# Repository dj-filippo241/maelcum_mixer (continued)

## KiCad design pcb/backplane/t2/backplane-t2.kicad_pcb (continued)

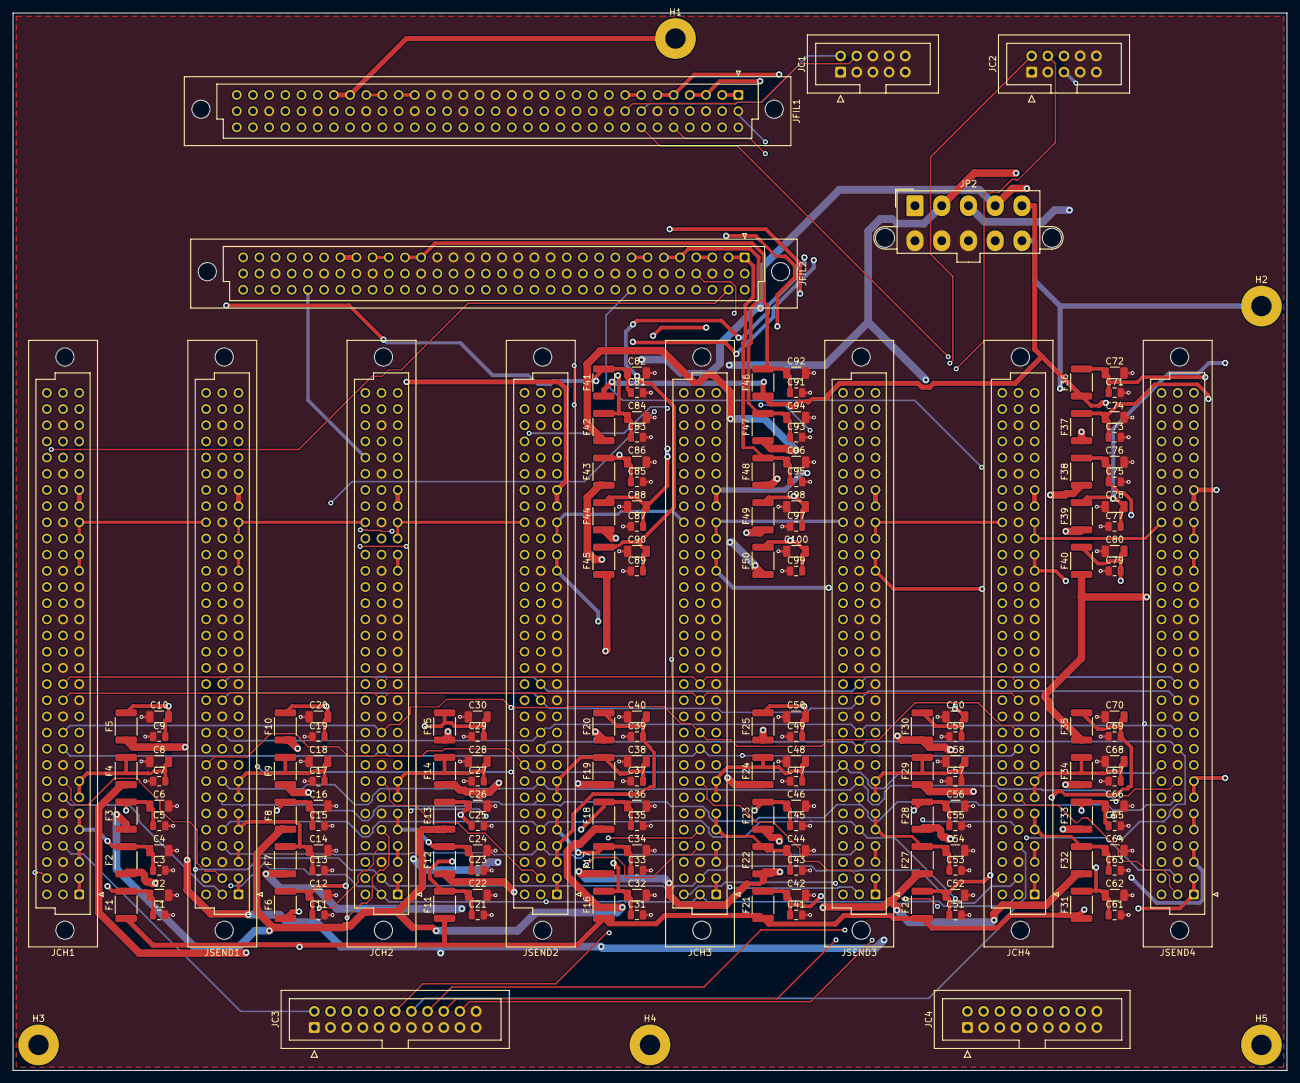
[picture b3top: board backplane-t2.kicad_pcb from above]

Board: 4 copper layers, 200.0 x 166.0 mm, 170 parts (0 on the bottom side), 99 nets.

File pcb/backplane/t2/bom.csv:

quantita;valore;impronta;riferimenti;nota
50;100n 50V;C_0805_2012Metric;C1 C3 C5 C7 C9 C11 C13 C15 C17 C19 C21 C23 C25 C27 C29 C31 C33 C35 C37 C39 C41 C43 C45 C47 C49 C51 C53 C55 C57 C59 C61 C63 C65 C67 C69 C71 C73 C75 C77 C79 C81 C83 C85 C87 C89 C91 C93 C95 C97 C99;bypass di slot (backplane §8)
50;10u 50V X7R;C_1206_3216Metric;C2 C4 C6 C8 C10 C12 C14 C16 C18 C20 C22 C24 C26 C28 C30 C32 C34 C36 C38 C40 C42 C44 C46 C48 C50 C52 C54 C56 C58 C60 C62 C64 C66 C68 C70 C72 C74 C76 C78 C80 C82 C84 C86 C88 C90 C92 C94 C96 C98 C100;bulk di slot (backplane §8); NOTA: MLCC 50 V
4;PTC 0.2 A;Fuse_1812_4532Metric;F1 F11 F21 F31;PTC di slot (psu-esterno §4.3); NOTA: tenuta 0.2 A, >= 33 V, 1812
18;PTC 0.1 A;Fuse_1812_4532Metric;F2 F4 F8 F10 F12 F14 F18 F20 F22 F24 F28 F30 F32 F34 F38 F40 F41 F46;PTC di slot (psu-esterno §4.3); NOTA: tenuta 0.1 A, >= 33 V, 1812
16;PTC 0.3 A;Fuse_1812_4532Metric;F3 F5 F13 F15 F23 F25 F33 F35 F42 F43 F44 F45 F47 F48 F49 F50;PTC di slot (psu-esterno §4.3); NOTA: tenuta 0.3 A, >= 33 V, 1812
12;PTC 0.05 A;Fuse_1812_4532Metric;F6 F7 F9 F16 F17 F19 F26 F27 F29 F36 F37 F39;PTC di slot (psu-esterno §4.3); NOTA: tenuta 0.05 A, >= 33 V, 1812
1;cavo C1 T1-T2 (VE);IDC-Header_2x05_P2.54mm_Vertical;JC1;NOTA: cavo piatto, ogni segnale fra due fili di massa; solo net a massa virtuale
1;cavo C2 T1-T2 (pilotato);IDC-Header_2x05_P2.54mm_Vertical;JC2;NOTA: cavo piatto, ogni segnale fra due fili di massa; solo linee pilotate
1;cavo C3 T2-T3 (pilotato);IDC-Header_2x11_P2.54mm_Vertical;JC3;NOTA: cavo piatto, ogni segnale fra due fili di massa; solo linee pilotate
1;cavo C4 T2-T4 (VE);IDC-Header_2x09_P2.54mm_Vertical;JC4;NOTA: cavo piatto, ogni segnale fra due fili di massa; solo net a massa virtuale
1;C96 femmina CH1;DIN41612_C_3x32_Female_Vertical_THT;JCH1;slot CH1, classe canale; pin da pcb/canale (netlist). Fila a a 2.11 mm dal piano medio della scheda di modulo, lato F del modulo verso la fila c (Harting 09 03 196 6921)
1;C96 femmina CH2;DIN41612_C_3x32_Female_Vertical_THT;JCH2;slot CH2, classe canale; pin da pcb/canale (netlist). Fila a a 2.11 mm dal piano medio della scheda di modulo, lato F del modulo verso la fila c (Harting 09 03 196 6921)
1;C96 femmina CH3;DIN41612_C_3x32_Female_Vertical_THT;JCH3;slot CH3, classe canale; pin da pcb/canale (netlist). Fila a a 2.11 mm dal piano medio della scheda di modulo, lato F del modulo verso la fila c (Harting 09 03 196 6921)
1;C96 femmina CH4;DIN41612_C_3x32_Female_Vertical_THT;JCH4;slot CH4, classe canale; pin da pcb/canale (netlist). Fila a a 2.11 mm dal piano medio della scheda di modulo, lato F del modulo verso la fila c (Harting 09 03 196 6921)
1;C96 femmina FIL1;DIN41612_C_3x32_Female_Vertical_THT;JFIL1;slot FIL1, classe filtro; pin da pcb/filtro/HPF (netlist). Fila a a 2.11 mm dal piano medio della scheda di modulo, lato F del modulo verso la fila c (Harting 09 03 196 6921)
1;C96 femmina FIL2;DIN41612_C_3x32_Female_Vertical_THT;JFIL2;slot FIL2, classe filtro; pin da pcb/filtro/LPF (netlist). Fila a a 2.11 mm dal piano medio della scheda di modulo, lato F del modulo verso la fila c (Harting 09 03 196 6921)
1;potenza P2 T1-T2;Molex_Mini-Fit_Jr_5566-10A2_2x05_P4.20mm_Vertical;JP2;NOTA: Mini-Fit Jr 2x5; radiale AGND del tratto fino alla stella del PSU-IN (grounding §2)
1;C96 femmina SEND1;DIN41612_C_3x32_Female_Vertical_THT;JSEND1;slot SEND1, classe fx-send; pin da pcb/fx-send (netlist). Fila a a 2.11 mm dal piano medio della scheda di modulo, lato F del modulo verso la fila c (Harting 09 03 196 6921)
1;C96 femmina SEND2;DIN41612_C_3x32_Female_Vertical_THT;JSEND2;slot SEND2, classe fx-send; pin da pcb/fx-send (netlist). Fila a a 2.11 mm dal piano medio della scheda di modulo, lato F del modulo verso la fila c (Harting 09 03 196 6921)
1;C96 femmina SEND3;DIN41612_C_3x32_Female_Vertical_THT;JSEND3;slot SEND3, classe fx-send; pin da pcb/fx-send (netlist). Fila a a 2.11 mm dal piano medio della scheda di modulo, lato F del modulo verso la fila c (Harting 09 03 196 6921)
1;C96 femmina SEND4;DIN41612_C_3x32_Female_Vertical_THT;JSEND4;slot SEND4, classe fx-send; pin da pcb/fx-send (netlist). Fila a a 2.11 mm dal piano medio della scheda di modulo, lato F del modulo verso la fila c (Harting 09 03 196 6921)

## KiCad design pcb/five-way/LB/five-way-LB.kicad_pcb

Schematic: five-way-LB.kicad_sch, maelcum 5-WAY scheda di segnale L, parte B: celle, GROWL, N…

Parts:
C1, C2: 220u 35V; CP_Radial_D8.0mm_P3.50mm
C3: 47u 10V; CP_Radial_D5.0mm_P2.00mm
C4, C8: 10u 35V; CP_Radial_D5.0mm_P2.00mm
C5, C9: 47u 35V; CP_Radial_D6.3mm_P2.50mm
C6, C10: 470u 25V; CP_Radial_D8.0mm_P3.50mm
C7, C11: 100u 25V; CP_Radial_D6.3mm_P2.50mm
C12, C13: 1u 50V; C_1206_3216Metric
C14, C15: 1u 25V; C_1206_3216Metric
C16, C17, C19, C20: 4u7 25V; C_1206_3216Metric
C18, C21: 10u 25V; C_1206_3216Metric
C22: 1u; C_1206_3216Metric
C23, C24, C25, C26, C27, C28, C29, C30, C35, C36, C37, C38, C39, C40, C45, C46, C47, C48, C49, C50, C55, C56, C57, C58, C59, C60, C65, C66, C67, C68, C69, C70, C75, C76, C77, C78, C79, C80, C88, C89, C90, C91, C104, C105, C106, C107, C108, C109, C110, C111, C113, C114: 100n; C_0805_2012Metric
C31, C33: 680n film; C_1812_4532Metric
C32, C34, C42, C44, C52, C54, C62, C64, C72, C74, C81, C83, C112: 100n film; C_1812_4532Metric
C41, C43, C101, C102, C103: 180n film; C_1812_4532Metric
C51, C53: 56n film; C_1812_4532Metric
C61, C63: 18n C0G; C_1206_3216Metric
C71, C73: 4n7 C0G; C_1206_3216Metric
C82, C84: 47n film; C_1812_4532Metric
C85: 6n8 C0G; C_1206_3216Metric
C86: 22u NP; CP_Radial_D6.3mm_P2.50mm
C87: 10u NP; CP_Radial_D6.3mm_P2.50mm
C92, C93, C94: 150n film; C_1812_4532Metric
C95: 1n5 C0G; C_1206_3216Metric
C96, C100: 5n1 C0G; C_1206_3216Metric
C97: 2200u 10V; CP_Radial_D10.0mm_P5.00mm
C98: 10u 25V; CP_Radial_D5.0mm_P2.00mm
C99: 1n8 C0G; C_1206_3216Metric
D1, D3, D6, D7, D8, D9, D10, D11, D12, D13, D14, D15, D16, D17, D18, D19, D20, D21, D22, D23, D24, D25, D26, D27, D28, D29, D30: 1N4148W; D_SOD-123
D2, D4: S1G; D_SMA
D5: LM4040-5.0; SOT-23
FB1, FB2, FB3, FB4, FB5: ferrite 600R; L_1206_3216Metric
H1, H2, H3: CHASSIS; MountingHole_3.2mm_M3_Pad
J1: C96 maschio; DIN41612_C_3x32_Male_Horizontal_THT
J2: 2x31 cavo piatto; PinHeader_2x31_P2.54mm_Vertical
Q1, Q2, Q3, Q4, Q5, Q6, Q7, Q8, Q9, Q10: LSK389 (dual); SOIC-8_3.9x4.9mm_P1.27mm
Q11: MMBFJ310; SOT-23
Q140: BD139; TO-126-3_Vertical
Q141: BD140; TO-126-3_Vertical
R1, R4: 120 1%; R_0805_2012Metric
R2, R5: 1k74 1%; R_0805_2012Metric
R3, R6, R242: 1k; R_0805_2012Metric
R7, R8: 150k 0.1%; R_0805_2012Metric
R9, R213: 1k5; R_0805_2012Metric
R10, R11, R23, R33, R43, R53, R63, R65, R67, R84, R85, R87, R89, R106, R107, R109, R111, R128, R129, R131, R133, R150, R151, R153, R155, R172, R173, R178, R179, R180, R181, R193, R194, R195, R201, R203, R205, R207, R209, R219, R221, R222, R224, R226, R228, R230, R231, R238: 10k 0.1%; R_0805_2012Metric
R12, R22, R32, R42, R52, R62: 49k9 0.1%; R_0805_2012Metric
R13: 1k02 0.1%; R_0805_2012Metric
R14, R24, R34, R44, R54, R241: 100k; R_0805_2012Metric
R15, R35: 24k3 0.1%; R_0805_2012Metric
R16, R36, R200, R202, R204: 36k5 0.1%; R_0805_2012Metric
R17, R37: 267k 0.1%; R_0805_2012Metric
R18, R38: 22k1 0.1%; R_0805_2012Metric
R19, R39: 57k6 0.1%; R_0805_2012Metric
R20, R40: 13k0 0.1%; R_0805_2012Metric
R21, R41, R48: 20k5 0.1%; R_0805_2012Metric
R25: 27k4 0.1%; R_0805_2012Metric
R26: 47k5 0.1%; R_0805_2012Metric
R27: 340k 0.1%; R_0805_2012Metric
R28, R66, R88, R110, R132, R154: 30k1 0.1%; R_0805_2012Metric
R29: 76k8 0.1%; R_0805_2012Metric
R30, R51, R58: 18k7 0.1%; R_0805_2012Metric
R31: 28k7 0.1%; R_0805_2012Metric
R45: 23k7 0.1%; R_0805_2012Metric
R46: 34k8 0.1%; R_0805_2012Metric
R47: 255k 0.1%; R_0805_2012Metric
R49: 53k6 0.1%; R_0805_2012Metric
R50: 12k1 0.1%; R_0805_2012Metric
R55: 23k2 0.1%; R_0805_2012Metric
R56: 32k4 0.1%; R_0805_2012Metric
R57: 232k 0.1%; R_0805_2012Metric
R59: 48k7 0.1%; R_0805_2012Metric
R60: 10k7 0.1%; R_0805_2012Metric
R61: 16k9 0.1%; R_0805_2012Metric
R64, R86, R108, R130, R152: 40k2 0.1%; R_0805_2012Metric
R68, R69, R70, R71, R73, R74, R75, R76, R90, R91, R92, R93, R95, R96, R97, R98, R112, R113, R114, R115, R117, R118, R119, R120, R134, R135, R136, R137, R139, R140, R141, R142, R156, R157, R158, R159, R161, R162, R163, R164: 100k 0.1%; R_0805_2012Metric
R72, R77: 117k 0.1%; R_0805_2012Metric
R78, R100, R122, R144, R166: 110 0.1%; R_0805_2012Metric
R79, R101, R123, R145, R167: 1k8 0.1%; R_0805_2012Metric
R80, R102, R124, R146, R168: 200 0.1%; R_0805_2012Metric
R81, R82, R103, R104, R125, R126, R147, R148, R169, R170, R206: 2k 0.1%; R_0805_2012Metric
R83, R105, R127, R149, R171: 1k62 0.1%; R_0805_2012Metric
R94, R99, R138, R143: 110k 0.1%; R_0805_2012Metric
R116, R121, R160, R165: 113k 0.1%; R_0805_2012Metric
R174, R175, R176, R177, R182: 9k31 0.1%; R_0805_2012Metric
R183, R210: 1k 0.1%; R_0805_2012Metric
R184: 47k; R_0805_2012Metric
R185, R186: 470; R_0805_2012Metric
R187, R229: 4k99 0.1%; R_0805_2012Metric
R188, R212: 10k; R_0805_2012Metric
R189, R190: 4k7; R_0805_2012Metric
R191: 11k1 0.1%; R_0805_2012Metric
R192, R208, R220, R239: 20k 0.1%; R_0805_2012Metric
R196, R233, R240: 1M; R_0805_2012Metric
R197, R198, R199, R234, R235, R236: 2k2 0.1%; R_0805_2012Metric
R211: 7k5; R_0805_2012Metric
R214: 150; R_0805_2012Metric
R215: 910; R_0805_2012Metric
R216: 48k7; R_0805_2012Metric
R217: 9k53; R_0805_2012Metric
R218: 4k87 0.1%; R_0805_2012Metric
R223, R225, R227: 19k6 0.1%; R_0805_2012Metric
R232: 1k8; R_0805_2012Metric
R237: 33; R_0805_2012Metric
R243: 47; R_0805_2012Metric
R244: 100; R_0805_2012Metric
U1, U2, U3, U5, U6, U8, U9, U11, U12, U14, U15, U17, U18, U19, U20, U21, U22, U23: OPA1654AIDR; SOIC-14_3.9x8.7mm_P1.27mm
U4, U7, U10, U13, U16, U24, U146: OPA1612AIDR; SOIC-8_3.9x4.9mm_P1.27mm
U25: OPA1642AIDR; SOIC-8_3.9x4.9mm_P1.27mm
U140: LM317; TO-220-3_Vertical
U141: LM337; TO-220-3_Vertical
U142: 78L15; SOT-89-3
U143: 79L15; SOT-89-3
U144: LT3045EMSE; MSOP-12-1EP_3x4.039mm_P0.65mm_EP1.651x2.845mm
U145: LT3094EMSE; MSOP-12-1EP_3x4.039mm_P0.65mm_EP1.651x2.845mm

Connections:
5W_MET_L: J2.55, R244.2
5W_OUT_L: J1.b4, R243.2
5W_SUM_L: J1.b7, R64.1, R84.1
+5V: FB5.1, J1.a21, J1.a22
+5VF: C3.1, FB5.2, J2.60
+15LN: C18.1, C23.1, C25.1, C27.1, C29.1, J2.57, R9.1, U1.4 (V+), U2.4 (V+), U3.4 (V+), U144.10 (OUTS), U144.11 (OUT), U144.12 (OUT), U146.8 (V+)
+15SW: C14.1, U142.1 (OUT)
+18V: C7.1, C17.1, C35.1, C37.1, C39.1, C45.1, C47.1, C49.1, C55.1, C57.1, C59.1, C65.1, C67.1, C69.1, C75.1, C77.1, C79.1, C88.1, C90.1, C104.1, C106.1, C108.1, C110.1, C113.1, Q140.1 (E), R213.1, U4.8 (V+), U5.4 (V+), U6.4 (V+), U7.8 (V+), U8.4 (V+), U9.4 (V+), U10.8 (V+), U11.4 (V+), U12.4 (V+), U13.8 (V+), U14.4 (V+), U15.4 (V+), U16.8 (V+), U17.4 (V+), U18.4 (V+), U19.4 (V+), U20.4 (V+), U21.4 (V+), U22.4 (V+), U23.4 (V+), U24.8 (V+), U25.8 (V+), U144.1 (IN), U144.2 (IN), U144.3 (IN), U144.4 (EN/UV), U144.7 (PGFB)
+REF5: J2.2, R10.1, R12.1, R22.1, R32.1, R42.1, R52.1, R62.1, U146.1, U146.2 (-)
-15LN: C21.2, C24.2, C26.2, C28.2, C30.2, J2.59, U1.11 (V-), U2.11 (V-), U3.11 (V-), U145.10 (OUTS), U145.11 (OUT), U145.12 (OUT), U146.4 (V-)
-15SW: C15.2, U143.3 (VO)
-18V: C11.2, C20.2, C36.2, C38.2, C40.2, C46.2, C48.2, C50.2, C56.2, C58.2, C60.2, C66.2, C68.2, C70.2, C76.2, C78.2, C80.2, C89.2, C91.2, C105.2, C107.2, C109.2, C111.2, C114.2, Q141.1 (E), U4.4 (V-), U5.11 (V-), U6.11 (V-), U7.4 (V-), U8.11 (V-), U9.11 (V-), U10.4 (V-), U11.11 (V-), U12.11 (V-), U13.4 (V-), U14.11 (V-), U15.11 (V-), U16.4 (V-), U17.11 (V-), U18.11 (V-), U19.11 (V-), U20.11 (V-), U21.11 (V-), U22.11 (V-), U23.11 (V-), U24.4 (V-), U25.4 (V-), U145.1 (IN), U145.2 (IN), U145.3 (EN/UV), U145.5 (PGFB), U145.13 (IN)
-REF5: R11.2, R17.2, R19.2, R21.2, R27.2, R29.2, R31.2, R37.2, R39.2, R41.2, R47.2, R49.2, R51.2, R57.2, R59.2, R61.2, U146.7
ADJ+: C4.1, D1.2 (A), R1.2, R2.1, U140.1 (ADJ)
ADJ-: C8.2, D3.1 (K), R4.2, R5.1, U141.1 (ADJ)
AGND: C1.2, C2.1, C4.2, C5.2, C6.2, C7.2, C8.1, C9.1, C10.1, C11.1, C12.2, C13.1, C14.2, C15.1, C16.2, C17.2, C18.2, C19.1, C20.1, C21.1, C22.2, C23.2, C24.1, C25.2, C26.1, C27.2, C28.1, C29.2, C30.1, C35.2, C36.1, C37.2, C38.1, C39.2, C40.1, C45.2, C46.1, C47.2, C48.1, C49.2, C50.1, C55.2, C56.1, C57.2, C58.1, C59.2, C60.1, C65.2, C66.1, C67.2, C68.1, C69.2, C70.1, C75.2, C76.1, C77.2, C78.1, C79.2, C80.1, C82.2, C84.2, C85.2, C88.2, C89.1, C90.2, C91.1, C95.2, C96.2, C97.2, C99.2, C100.2, C104.2, C105.1, C106.2, C107.1, C108.2, C109.1, C110.2, C111.1, C113.2, C114.1, D5.2 (A), J1.a13, J1.a14, J1.a15, J1.a16, J1.a17, J1.a18, J1.a19, J1.a20, J1.b3, J1.b6, J1.b9, J1.b12, J1.b15, J1.b18, J1.b21, J1.b24, J1.b27, J1.b30, J2.1, J2.10, J2.18, J2.26, J2.34, J2.42, J2.49, J2.54, J2.56, J2.58, J2.62, R2.2, R5.2, R7.2, R8.2, R13.2, R14.2, R24.2, R34.2, R44.2, R54.2, R78.2, R80.2, R100.2, R102.2, R122.2, R124.2, R144.2, R146.2, R166.2, R168.2, R179.2, R196.2, R201.2, R203.2, R205.2, R210.2, R215.2, R222.2, R224.2, R226.2, R229.2, R233.2, R242.2, U1.10 (+), U2.3 (+), U2.10 (+), U3.3 (+), U3.10 (+), U3.12 (+), U4.5 (+), U5.3 (+), U5.5 (+), U5.12 (+), U6.3 (+), U6.10 (+), U6.12 (+), U7.5 (+), U8.3 (+), U8.5 (+), U8.12 (+), U9.3 (+), U9.10 (+), U9.12 (+), U10.5 (+), U11.3 (+), U11.5 (+), U11.12 (+), U12.3 (+), U12.10 (+), U12.12 (+), U13.5 (+), U14.3 (+), U14.5 (+), U14.12 (+), U15.3 (+), U15.10 (+), U15.12 (+), U16.5 (+), U17.3 (+), U17.5 (+), U17.12 (+), U18.3 (+), U18.10 (+), U18.12 (+), U20.3 (+), U20.5 (+), U20.10 (+), U22.5 (+), U24.3 (+), U24.5 (+), U25.5 (+), U142.2 (GND), U143.1 (GND), U144.6 (ILIM), U144.9 (GND), U144.13 (GND), U145.6 (ILIM), U145.9 (GND), U146.5 (+)
BASE+: C6.1, Q140.3 (B), R3.2
BASE-: C10.2, Q141.3 (B), R6.2
BP1: C31.2, U5.7, U5.10 (+)
BP2: C41.2, U8.7, U8.10 (+)
BP3: C51.2, U11.7, U11.10 (+)
BP4: C61.2, U14.7, U14.10 (+)
BP5: C71.2, U17.7, U17.10 (+)
BPB1: J2.4, Q2.2 (D1), R73.1, U5.8, U5.9 (-)
BPB2: J2.12, Q4.2 (D1), R95.1, U8.8, U8.9 (-)
BPB3: J2.20, Q6.2 (D1), R117.1, U11.8, U11.9 (-)
BPB4: J2.28, Q8.2 (D1), R139.1, U14.8, U14.9 (-)
BPB5: J2.36, Q10.2 (D1), R161.1, U17.8, U17.9 (-)
CHASSIS: H1.1, H2.1, H3.1, J1.a25, J1.a26
CTRL_GND: C3.2, J1.a23, J1.a24, J1.c16, J1.c20, J1.c24, J1.c28, J2.61
DBG: R198.1, U20.13 (-), U20.14
DBT: R235.1, U23.13 (-), U23.14
DDG: J2.43, R195.2, U20.8
DQ1: J2.7, R79.1, R81.1, U4.1
DQ2: J2.15, R101.1, R103.1, U7.1
DQ3: J2.23, R123.1, R125.1, U10.1
DQ4: J2.31, R145.1, R147.1, U13.1
DQ5: J2.39, R167.1, R169.1, U16.1
DS1N: R197.2, R198.2, R199.1, U24.2 (-)
DS2N: R234.2, R235.2, R236.1, U24.6 (-)
DSEL: R231.2, R232.1, U23.8
DTP: J2.50, R232.2
DWG: J2.44, R196.1, U20.12 (+)
DWT: J2.51, R233.1, U23.12 (+)
DY1: C92.1, R199.2, R200.1, R230.1, R234.1, U24.1
DY2: R236.2, R237.1, U24.7
E1: R85.2, R86.1, R106.1, U6.14
E2: R107.2, R108.1, R128.1, U9.14
E3: R129.2, R130.1, R150.1, U12.14
E4: R151.2, R152.1, R172.1, U15.14
E5: R173.2, R174.1, R178.1, R197.1, U18.14
EDRV: R237.2, R238.1, R244.1
GA1: C81.1, R174.2, R175.1
GA2: C82.1, R175.2, U19.3 (+)
GB1: C83.1, R176.2, R177.1
GB2: C84.1, R177.2, U19.5 (+)
GDN: R191.2, R192.2, R193.2, R194.2, R195.1, U20.9 (-)
GLA1: D21.1 (K), R185.1
GLAC: C86.2, R191.1
GLB1: D22.1 (K), D23.2 (A)
GLB2: D23.1 (K), D24.2 (A)
GLB3: D24.1 (K), R186.1
GLGN: D21.2 (A), R183.2, R184.1, R186.2, U20.2 (-)
GLOUT: C86.1, D22.2 (A), R184.2, R185.2, U20.1
GLOW: C83.2, J2.45, R180.1, R193.1, U19.6 (-), U19.7
GLP1: C81.2, R176.1, U19.1, U19.2 (-)
GLR: J2.46, R183.1
GMA1: D25.1 (K), D26.2 (A)
GMA2: D26.1 (K), D27.2 (A)
GMA3: D27.1 (K), R189.1
GMAC: C87.2, R192.1
GMB1: D28.1 (K), D29.2 (A)
GMB2: D29.1 (K), D30.2 (A)
GMB3: D30.1 (K), R190.1
GMC: C85.1, R182.2, U19.12 (+)
GMGN: D25.2 (A), R187.2, R188.1, R190.2, U20.6 (-)
GMID: J2.47, R194.1, U19.13 (-), U19.14
GMOUT: C87.1, D28.2 (A), R188.2, R189.2, U20.7
GMR: J2.48, R187.1
GR1_1: Q1.8 (G2), R70.2, R71.2
GR1_2: Q2.8 (G2), R75.2, R76.2
GR2_1: Q3.8 (G2), R92.2, R93.2
GR2_2: Q4.8 (G2), R97.2, R98.2
GR3_1: Q5.8 (G2), R114.2, R115.2
GR3_2: Q6.8 (G2), R119.2, R120.2
GR4_1: Q7.8 (G2), R136.2, R137.2
GR4_2: Q8.8 (G2), R141.2, R142.2
GR5_1: Q9.8 (G2), R158.2, R159.2
GR5_2: Q10.8 (G2), R163.2, R164.2
GREST: R181.2, R182.1, U19.8
GRN: R180.2, R181.1, U19.9 (-)
GRP: R178.2, R179.1, U19.10 (+)
GS1_1: Q1.4 (G1), R68.2, R69.2
GS1_2: Q2.4 (G1), R73.2, R74.2
GS2_1: Q3.4 (G1), R90.2, R91.2
GS2_2: Q4.4 (G1), R95.2, R96.2
GS3_1: Q5.4 (G1), R112.2, R113.2
GS3_2: Q6.4 (G1), R117.2, R118.2
GS4_1: Q7.4 (G1), R134.2, R135.2
GS4_2: Q8.4 (G1), R139.2, R140.2
GS5_1: Q9.4 (G1), R156.2, R157.2
GS5_2: Q10.4 (G1), R161.2, R162.2
GW1: J2.8, R83.1
GW2: J2.16, R105.1
GW3: J2.24, R127.1
GW4: J2.32, R149.1
GW5: J2.40, R171.1
HP1: Q1.2 (D1), R67.2, R68.1, U5.1
HP2: Q3.2 (D1), R89.2, R90.1, U8.1
HP3: Q5.2 (D1), R111.2, R112.1, U11.1
HP4: Q7.2 (D1), R133.2, R134.1, U14.1
HP5: Q9.2 (D1), R155.2, R156.1, U17.1
LDRAIN: C98.1, Q11.1 (D), R213.2
LGATE: Q11.3 (G), R212.2
LJS1: Q11.2 (S), R214.1
LJS2: C97.1, R214.2, R215.1
LP1: C33.2, U6.1, U6.5 (+)
LP2: C43.2, U9.1, U9.5 (+)
LP3: C53.2, U12.1, U12.5 (+)
LP4: C63.2, U15.1, U15.5 (+)
LP5: C73.2, U18.1, U18.5 (+)
LPB1: R65.1, U6.6 (-), U6.7
LPB2: R87.1, U9.6 (-), U9.7
LPB3: R109.1, U12.6 (-), U12.7
LPB4: R131.1, U15.6 (-), U15.7
LPB5: R153.1, U18.6 (-), U18.7
LSN: J2.53, R210.1, R211.2, U22.2 (-)
LSP: J2.52, R211.1, R212.1, U22.1
LTAC: C98.2, R216.1
LTN: R216.2, R217.1, U22.6 (-)
MUP: R241.2, R242.1, U25.3 (+)
ND1: R218.2, R219.1, U22.10 (+)
ND1C: C99.1, R219.2
ND2C: C100.1, R221.2
ND2N: R220.2, R221.1, U22.9 (-)
ND3N: C101.2, R222.1, R223.2, U22.13 (-)
ND4N: C102.2, R224.1, R225.2, U23.2 (-)
ND5N: C103.2, R226.1, R227.2, U23.6 (-)
NDQ1: J2.9, R66.1, R82.2, U4.7
NDQ2: J2.17, R88.1, R104.2, U7.7
NDQ3: J2.25, R110.1, R126.2, U10.7
NDQ4: J2.33, R132.1, R148.2, U13.7
NDQ5: J2.41, R154.1, R170.2, U16.7
NE1: C92.2, R200.2, R201.1, U21.3 (+)
NE2: C93.2, R202.2, R203.1, U21.5 (+)
NE3: C94.2, R204.2, R205.1, U21.10 (+)
NE4: R206.2, R207.1, U21.12 (+)
NE4C: C95.1, R207.2
NE5C: C96.1, R209.2
NI1_1: C31.1, Q1.1 (S1), U5.6 (-)
NI1_2: C33.1, Q2.1 (S1), U6.2 (-)
NI2_1: C41.1, Q3.1 (S1), U8.6 (-)
NI2_2: C43.1, Q4.1 (S1), U9.2 (-)
NI3_1: C51.1, Q5.1 (S1), U11.6 (-)
NI3_2: C53.1, Q6.1 (S1), U12.2 (-)
NI4_1: C61.1, Q7.1 (S1), U14.6 (-)
NI4_2: C63.1, Q8.1 (S1), U15.2 (-)
NI5_1: C71.1, Q9.1 (S1), U17.6 (-)
NI5_2: C73.1, Q10.1 (S1), U18.2 (-)
NIQ1: R81.2, R82.1, U4.6 (-)
NIQ2: R103.2, R104.1, U7.6 (-)
NIQ3: R125.2, R126.1, U10.6 (-)
NIQ4: R147.2, R148.1, U13.6 (-)
NIQ5: R169.2, R170.1, U16.6 (-)
NMU: R238.2, R239.1, U25.2 (-)
NREF5I: R10.2, R11.1, U146.6 (-)
NS1: R64.2, R65.2, R66.2, R67.1, U5.2 (-)
NS2: R86.2, R87.2, R88.2, R89.1, U8.2 (-)
NS3: R108.2, R109.2, R110.2, R111.1, U11.2 (-)
NS4: R130.2, R131.2, R132.2, R133.1, U14.2 (-)
NS5: R152.2, R153.2, R154.2, R155.1, U17.2 (-)
NS21: R83.2, R84.2, R85.1, U6.13 (-)
NS22: R105.2, R106.2, R107.1, U9.13 (-)
NS23: R127.2, R128.2, R129.1, U12.13 (-)
NS24: R149.2, R150.2, R151.1, U15.13 (-)
NS25: R171.2, R172.2, R173.1, U18.13 (-)
NU1: C93.1, R202.1, U21.1, U21.2 (-)
NU2: C94.1, R204.1, U21.6 (-), U21.7
NU3: R206.1, U21.8, U21.9 (-)
NU3_1: U3.13 (-), U3.14
NU4: R208.1, U21.13 (-), U21.14
NUS: R208.2, R209.1, U22.3 (+)
NW: C103.1, R227.1, R228.1, U23.7
NW1: R79.2, R80.1, U4.2 (-)
NW2: R101.2, R102.1, R220.1, U7.2 (-), U22.8, U22.12 (+)
NW3: C101.1, R123.2, R124.1, R223.1, U10.2 (-), U22.14, U23.3 (+)
NW4: C102.1, R145.2, R146.1, R225.1, U13.2 (-), U23.1, U23.5 (+)
NW5: R167.2, R168.1, U16.2 (-)
NWN: R217.2, R218.1, U22.7
NXN: R230.2, R231.1, U23.9 (-)
NXP: R228.2, R229.1, U23.10 (+)
POSW1: J2.3, R14.1, U1.5 (+)
POSW2: J2.11, R24.1, U1.12 (+)
POSW3: J2.19, R34.1, U2.5 (+)
POSW4: J2.27, R44.1, U2.12 (+)
POSW5: J2.35, R54.1, U3.5 (+)
POSX1: R15.1, R16.1, R18.1, R20.1, U1.6 (-), U1.7
POSX2: R25.1, R26.1, R28.1, R30.1, U1.13 (-), U1.14
POSX3: R35.1, R36.1, R38.1, R40.1, U2.6 (-), U2.7
POSX4: R45.1, R46.1, R48.1, R50.1, U2.13 (-), U2.14
POSX5: R55.1, R56.1, R58.1, R60.1, U3.6 (-), U3.7
RAW+22: FB3.1, J1.a5, J1.a6
RAW+27: FB1.1, J1.a1, J1.a2
RAW-22: FB4.1, J1.a7, J1.a8
RAW-27: FB2.1, J1.a3, J1.a4
REF5K: C22.1, D5.1 (K), R9.2, U146.3 (+)
SETN: C19.2, R8.1, U145.8 (SET)
SETP: C16.1, R7.1, U144.8 (SET)
SH1: R23.2, R72.2, R77.2, U1.8
SH2: R33.2, R94.2, R99.2, U2.1
SH3: R43.2, R116.2, R121.2, U2.8
SH4: R53.2, R138.2, R143.2, U3.1
SH5: R63.2, R160.2, R165.2, U3.8
SJ1: D6.1 (K), D7.1 (K), D8.1 (K), R15.2, R22.2, R23.1, U1.9 (-)
SJ2: D9.1 (K), D10.1 (K), D11.1 (K), R25.2, R32.2, R33.1, U2.2 (-)
SJ3: D12.1 (K), D13.1 (K), D14.1 (K), R35.2, R42.2, R43.1, U2.9 (-)
SJ4: D15.1 (K), D16.1 (K), D17.1 (K), R45.2, R52.2, R53.1, U3.2 (-)
SJ5: D18.1 (K), D19.1 (K), D20.1 (K), R55.2, R62.2, R63.1, U3.9 (-)
SN1_1: D6.2 (A), R16.2, R17.1
SN1_2: D9.2 (A), R26.2, R27.1
SN1_3: D12.2 (A), R36.2, R37.1
SN1_4: D15.2 (A), R46.2, R47.1
SN1_5: D18.2 (A), R56.2, R57.1
SN2_1: D7.2 (A), R18.2, R19.1
SN2_2: D10.2 (A), R28.2, R29.1
SN2_3: D13.2 (A), R38.2, R39.1
SN2_4: D16.2 (A), R48.2, R49.1
SN2_5: D19.2 (A), R58.2, R59.1
SN3_1: D8.2 (A), R20.2, R21.1
SN3_2: D11.2 (A), R30.2, R31.1
SN3_3: D14.2 (A), R40.2, R41.1
SN3_4: D17.2 (A), R50.2, R51.1
SN3_5: D20.2 (A), R60.2, R61.1
SV1_1: C32.1, Q1.5 (S2), R72.1, U5.13 (-)
SV1_2: C34.1, Q2.5 (S2), R77.1, U6.9 (-)
SV2_1: C42.1, Q3.5 (S2), R94.1, U8.13 (-)
SV2_2: C44.1, Q4.5 (S2), R99.1, U9.9 (-)
SV3_1: C52.1, Q5.5 (S2), R116.1, U11.13 (-)
SV3_2: C54.1, Q6.5 (S2), R121.1, U12.9 (-)
SV4_1: C62.1, Q7.5 (S2), R138.1, U14.13 (-)
SV4_2: C64.1, Q8.5 (S2), R143.1, U15.9 (-)
SV5_1: C72.1, Q9.5 (S2), R160.1, U17.13 (-)
SV5_2: C74.1, Q10.5 (S2), R165.1, U18.9 (-)
SVI: C112.1, R240.2, U25.6 (-)
SVO: C112.2, R241.1, U25.7
V22F+: C12.1, FB3.2, U142.3 (IN)
V22F-: C13.2, FB4.2, U143.2 (VI)
V27F+: C1.1, D2.1 (K), FB1.2, U140.3 (VI)
V27F-: C2.2, D4.2 (A), FB2.2, U141.2 (VI)
VC1_1: C32.2, R69.1, R71.1, U5.14
VC1_2: C34.2, R74.1, R76.1, U6.8
VC2_1: C42.2, R91.1, R93.1, U8.14
VC2_2: C44.2, R96.1, R98.1, U9.8
VC3_1: C52.2, R113.1, R115.1, U11.14
VC3_2: C54.2, R118.1, R120.1, U12.8
VC4_1: C62.2, R135.1, R137.1, U14.14
VC4_2: C64.2, R140.1, R142.1, U15.8
VC5_1: C72.2, R157.1, R159.1, U17.14
VC5_2: C74.2, R162.1, R164.1, U18.8
VOUT: R239.2, R240.1, R243.1, U25.1
VRD: Q1.6 (D2), Q2.6 (D2), Q3.6 (D2), Q4.6 (D2), Q5.6 (D2), Q6.6 (D2), Q7.6 (D2), Q8.6 (D2), Q9.6 (D2), Q10.6 (D2), R70.1, R75.1, R92.1, R97.1, R114.1, R119.1, R136.1, R141.1, R158.1, R163.1, U1.1, U1.2 (-)
VRDD: R12.2, R13.1, U1.3 (+)
VREG+: C5.1, D1.1 (K), D2.2 (A), Q140.2 (C), R1.1, R3.1, U140.2 (VO)
VREG-: C9.2, D3.2 (A), D4.1 (K), Q141.2 (C), R4.1, R6.1, U141.3 (VO)
WB1: J2.6, R78.1
WB2: J2.14, R100.1
WB3: J2.22, R122.1
WB4: J2.30, R144.1
WB5: J2.38, R166.1
WW1: J2.5, U4.3 (+)
WW2: J2.13, U7.3 (+)
WW3: J2.21, U10.3 (+)
WW4: J2.29, U13.3 (+)
WW5: J2.37, U16.3 (+)

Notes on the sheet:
BACKPLANE C96 (classe 5-WAY, sistema-backplane §4)
ALIMENTAZIONE +-18 audio, +-15 switch, +5, +-15 LN, +-5 riferimento
POSITION: shaper a diodi per banda e riferimento di drain 0,1 V dei replica (REV todo 50)
CELLA 1 (v0.2.2, §4.2-4.3)
CELLA 2 (v0.2.2, §4.2-4.3)
CELLA 3 (v0.2.2, §4.2-4.3)
CELLA 4 (v0.2.2, §4.2-4.3)
CELLA 5 (v0.2.2, §4.2-4.3)
GROWL A BANDE (dec. 165, 175; growl-bande.cir, module-noise-b9.cir)
NASTRO A BANDE B9 (dec. 166, 175; nastro-b9.cir, module-noise-b9.cir)
MAKE-UP +6 dB, servo DC (§5bis.7) e uscita verso MSUM1
CAVO SCHEDA COMANDI (J2)

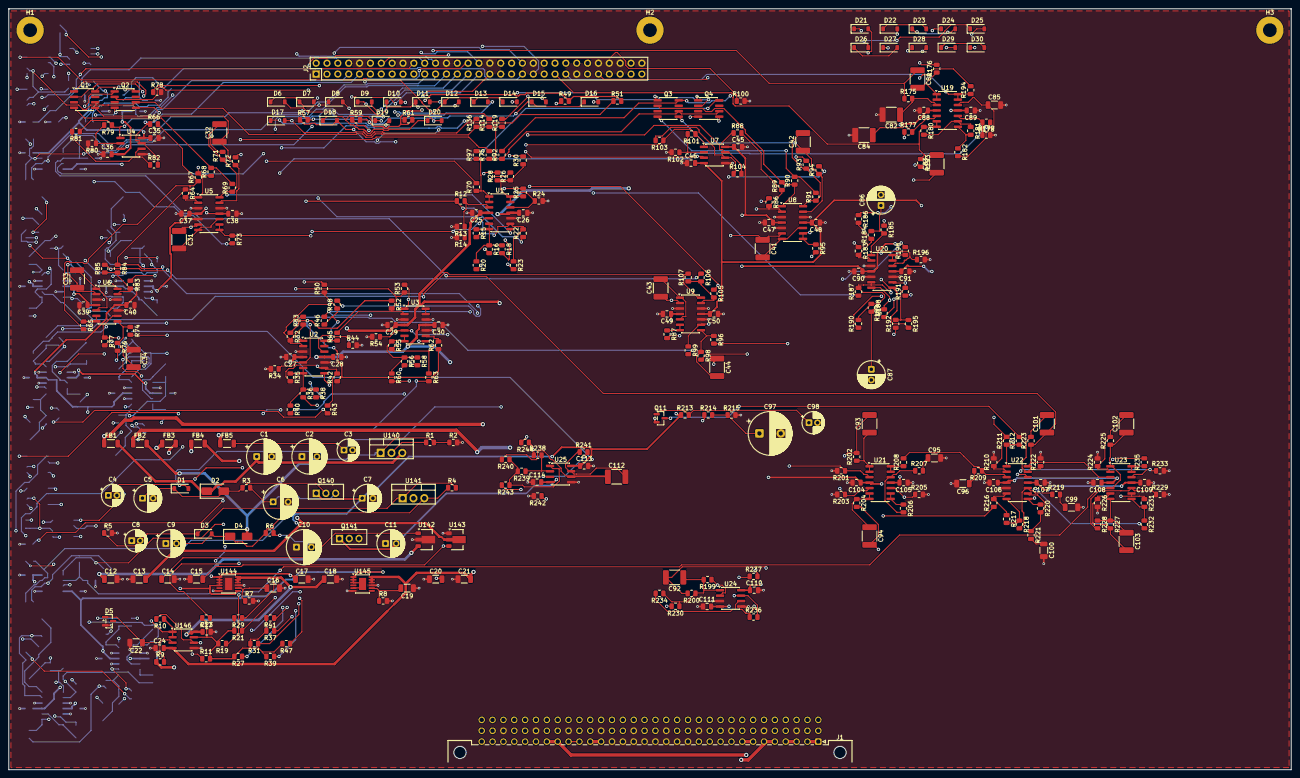
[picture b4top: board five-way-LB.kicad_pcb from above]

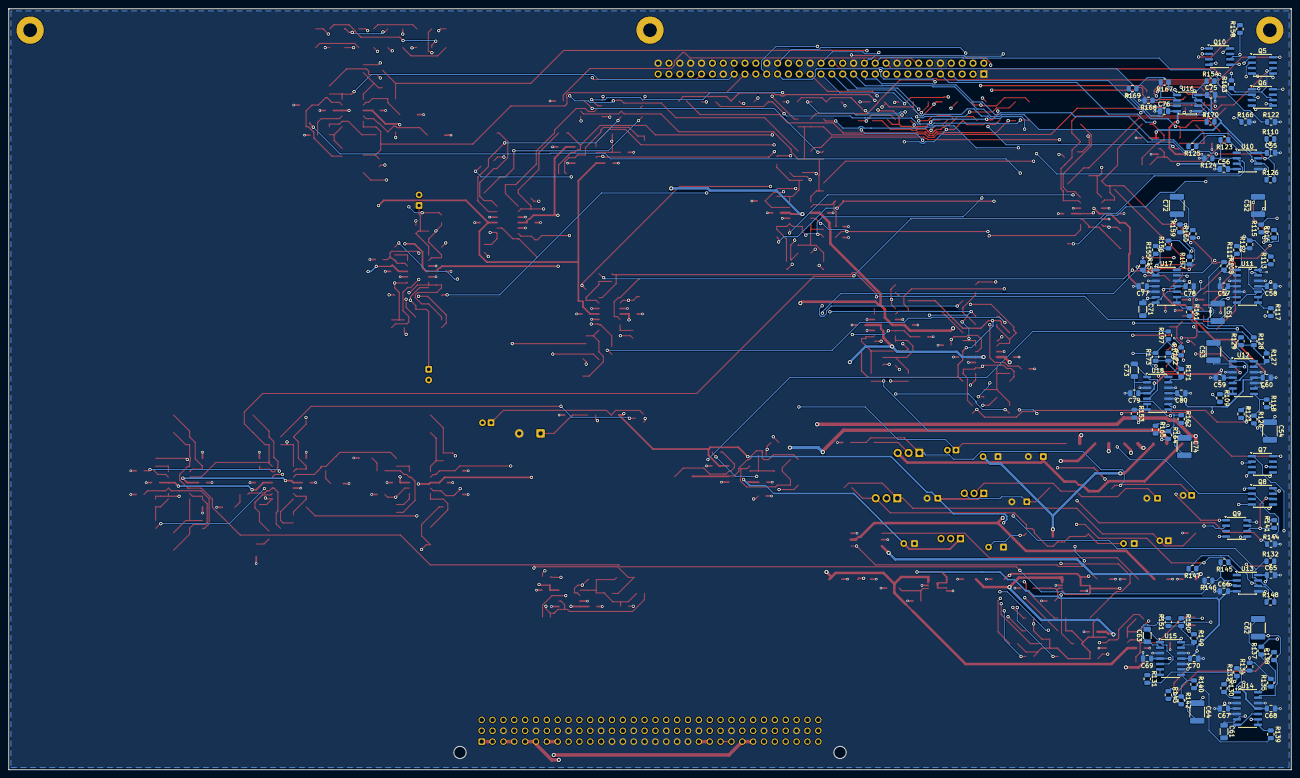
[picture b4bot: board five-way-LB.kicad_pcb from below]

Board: 4 copper layers, 300.0 x 178.0 mm, 443 parts (110 on the bottom side), 274 nets.

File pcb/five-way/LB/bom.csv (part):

quantita;valore;impronta;riferimenti;nota
2;220u 35V;CP_Radial_D8.0mm_P3.50mm;C1 C2;
1;100n film;C_1812_4532Metric;C112;integratore 1M / 100n film
2;1u 50V;C_1206_3216Metric;C12 C13;
2;1u 25V;C_1206_3216Metric;C14 C15;
1;4u7 25V;C_1206_3216Metric;C16;rumore del riferimento (datasheet: 4,7 uF)
3;4u7 25V;C_1206_3216Metric;C17 C19 C20;
2;10u 25V;C_1206_3216Metric;C18 C21;
1;1u;C_1206_3216Metric;C22;
52;100n;C_0805_2012Metric;C23 C24 C25 C26 C27 C28 C29 C30 C35 C36 C37 C38 C39 C40 C45 C46 C47 C48 C49 C50 C55 C56 C57 C58 C59 C60 C65 C66 C67 C68 C69 C70 C75 C76 C77 C78 C79 C80 C88 C89 C90 C91 C104 C105 C106 C107 C108 C109 C110 C111 C113 C114;
1;47u 10V;CP_Radial_D5.0mm_P2.00mm;C3;
1;680n film;C_1812_4532Metric;C31;Cint
12;100n film;C_1812_4532Metric;C32 C34 C42 C44 C52 C54 C62 C64 C72 C74 C81 C83;
1;680n film;C_1812_4532Metric;C33;
2;10u 35V;CP_Radial_D5.0mm_P2.00mm;C4 C8;
1;180n film;C_1812_4532Metric;C41;Cint
4;180n film;C_1812_4532Metric;C43 C101 C102 C103;
2;47u 35V;CP_Radial_D6.3mm_P2.50mm;C5 C9;
1;56n film;C_1812_4532Metric;C51;Cint
1;56n film;C_1812_4532Metric;C53;
2;470u 25V;CP_Radial_D8.0mm_P3.50mm;C6 C10;
1;18n C0G;C_1206_3216Metric;C61;Cint
1;18n C0G;C_1206_3216Metric;C63;
2;100u 25V;CP_Radial_D6.3mm_P2.50mm;C7 C11;
1;4n7 C0G;C_1206_3216Metric;C71;Cint
1;4n7 C0G;C_1206_3216Metric;C73;
2;47n film;C_1812_4532Metric;C82 C84;
1;6n8 C0G;C_1206_3216Metric;C85;polo 2,5 kHz (9,31k / 6,8n = 2,51 kHz)
1;22u NP;CP_Radial_D6.3mm_P2.50mm;C86;NOTA: 22u bipolare (sim 14,3u): polo < 1 Hz
1;10u NP;CP_Radial_D6.3mm_P2.50mm;C87;NOTA: 10u bipolare (sim 8u)
3;150n film;C_1812_4532Metric;C92 C93 C94;
1;1n5 C0G;C_1206_3216Metric;C95;
2;5n1 C0G;C_1206_3216Metric;C96 C100;
1;2200u 10V;CP_Radial_D10.0mm_P5.00mm;C97;
1;10u 25V;CP_Radial_D5.0mm_P2.00mm;C98;
1;1n8 C0G;C_1206_3216Metric;C99;
1;1N4148W;D_SOD-123;D1;scarica Cadj
1;S1G;D_SMA;D2;protezione inversa
26;1N4148W;D_SOD-123;D3 D6 D7 D8 D9 D10 D11 D12 D13 D14 D15 D16 D17 D18 D19 D20 D21 D22 D23 D24 D25 D26 D27 D28 D29 D30;
1;S1G;D_SMA;D4;
1;LM4040-5.0;SOT-23;D5;
5;ferrite 600R;L_1206_3216Metric;FB1 FB2 FB3 FB4 FB5;
1;C96 maschio;DIN41612_C_3x32_Male_Horizontal_THT;J1;DIN 41612 C 3x32, angolo retto; lato L del 5-way, parte B
1;2x31 cavo piatto;PinHeader_2x31_P2.54mm_Vertical;J2;cavo piatto corto verso la scheda comandi dietro il pannello (dec. 133)
10;LSK389 (dual);SOIC-8_3.9x4.9mm_P1.27mm;Q1 Q2 Q3 Q4 Q5 Q6 Q7 Q8 Q9 Q10;JFET di segnale (1) e replica (2) nello stesso die (REV todo 50); bin Idss/Vp
1;MMBFJ310;SOT-23;Q11;NJ310 in sim; simbolo MMBFJ113 (1 D, 2 S, 3 G) = MMBFJ310L onsemi, SOT-23 case 318 style 10 (todo 339)
1;BD139;TO-126-3_Vertical;Q140;
1;BD140;TO-126-3_Vertical;Q141;
2;120 1%;R_0805_2012Metric;R1 R4;
48;10k 0.1%;R_0805_2012Metric;R10 R11 R23 R33 R43 R53 R63 R65 R67 R84 R85 R87 R89 R106 R107 R109 R111 R128 R129 R131 R133 R150 R151 R153 R155 R172 R173 R178 R179 R180 R181 R193 R194 R195 R201 R203 R205 R207 R209 R219 R221 R222 R224 R226 R228 R230 R231 R238;
4;113k 0.1%;R_0805_2012Metric;R116 R121 R160 R165;Ictl = |SH|/R: f0 proporzionale (replica-a.cir)
1;49k9 0.1%;R_0805_2012Metric;R12;Vds dei replica: 5 x 1,02/50,92 = 0,1002 V
1;1k02 0.1%;R_0805_2012Metric;R13;
5;100k;R_0805_2012Metric;R14 R24 R34 R44 R54;pot staccato = inizio corsa
1;24k3 0.1%;R_0805_2012Metric;R15;shaper_fit.py: f = lo (hi/lo)^theta, entro +-1 % a 35 C
4;36k5 0.1%;R_0805_2012Metric;R16 R36 R202 R204;
2;267k 0.1%;R_0805_2012Metric;R17 R37;
1;9k31 0.1%;R_0805_2012Metric;R174;NOTA: LP 250 Hz con C E12 100n/47n e R 9,31k (Q 0,73)
4;9k31 0.1%;R_0805_2012Metric;R175 R176 R177 R182;
2;22k1 0.1%;R_0805_2012Metric;R18 R38;
1;1k 0.1%;R_0805_2012Metric;R183;spinta dei bassi: 1k + reostato 10k sul cavo (11k -> 1k, NOTA)
1;47k;R_0805_2012Metric;R184;
2;470;R_0805_2012Metric;R185 R186;
1;4k99 0.1%;R_0805_2012Metric;R187;spinta dei medi: 4,99k + reostato 5k sul cavo
2;10k;R_0805_2012Metric;R188 R212;
2;4k7;R_0805_2012Metric;R189 R190;
2;57k6 0.1%;R_0805_2012Metric;R19 R39;
1;11k1 0.1%;R_0805_2012Metric;R191;
3;20k 0.1%;R_0805_2012Metric;R192 R220 R239;
1;1M;R_0805_2012Metric;R196;pot staccato = GROWL a zero
6;2k2 0.1%;R_0805_2012Metric;R197 R198 R199 R234 R235 R236;
1;1k74 1%;R_0805_2012Metric;R2;E96 1,74k = 19,4 V (fx-send NOTE punto 16)
2;13k0 0.1%;R_0805_2012Metric;R20 R40;
1;36k5 0.1%;R_0805_2012Metric;R200;NOTA: 150n E12 (sim 144,7n): fz 28,9 Hz
1;2k 0.1%;R_0805_2012Metric;R206;taglio dei super: polo 10,8k / zero 9k
1;20k 0.1%;R_0805_2012Metric;R208;inclinazione dei medi (fmt 1 kHz, rt 3)
3;20k5 0.1%;R_0805_2012Metric;R21 R41 R48;
1;1k 0.1%;R_0805_2012Metric;R210;
1;7k5;R_0805_2012Metric;R211;NOTA: reostato 5k // 7,5k = 0..3,0k (+12 dB a fine corsa)
1;1k5;R_0805_2012Metric;R213;
1;150;R_0805_2012Metric;R214;
1;910;R_0805_2012Metric;R215;sim 900
1;48k7;R_0805_2012Metric;R216;10k/kt, kt 0,206 (dispersione del JFET: trim a banco, §5bis.6)
1;9k53;R_0805_2012Metric;R217;10k kl/kt
1;4k87 0.1%;R_0805_2012Metric;R218;
5;49k9 0.1%;R_0805_2012Metric;R22 R32 R42 R52 R62;offset: -1 V a inizio corsa (Ictl minima)
1;19k6 0.1%;R_0805_2012Metric;R223;NOTA: 180n E12 (sim 172n): fp 134 Hz
2;19k6 0.1%;R_0805_2012Metric;R225 R227;
1;4k99 0.1%;R_0805_2012Metric;R229;kv = -3,5 dB
1;1k8;R_0805_2012Metric;R232;mt = 0,85 a fine corsa
1;1M;R_0805_2012Metric;R233;pot staccato = NASTRO a zero
1;33;R_0805_2012Metric;R237;
1;1M;R_0805_2012Metric;R240;
1;100k;R_0805_2012Metric;R241;
1;1k;R_0805_2012Metric;R242;partitore del servo: corsa +-385 mV
1;47;R_0805_2012Metric;R243;NOTA: 47R verso MSUM1 (20k sul master); ponticello J5W sul backplane
1;100;R_0805_2012Metric;R244;presa del meter verso i LED di livello sulla scheda comandi
1;27k4 0.1%;R_0805_2012Metric;R25;
1;47k5 0.1%;R_0805_2012Metric;R26;
1;340k 0.1%;R_0805_2012Metric;R27;
1;30k1 0.1%;R_0805_2012Metric;R28;
1;76k8 0.1%;R_0805_2012Metric;R29;
1;1k;R_0805_2012Metric;R3;NOTA: cap-moltiplicatore come il FX-SEND (~50 mA)
3;18k7 0.1%;R_0805_2012Metric;R30 R51 R58;
1;28k7 0.1%;R_0805_2012Metric;R31;
1;24k3 0.1%;R_0805_2012Metric;R35;
1;23k7 0.1%;R_0805_2012Metric;R45;
1;34k8 0.1%;R_0805_2012Metric;R46;
1;255k 0.1%;R_0805_2012Metric;R47;
1;53k6 0.1%;R_0805_2012Metric;R49;
1;1k74 1%;R_0805_2012Metric;R5;
1;12k1 0.1%;R_0805_2012Metric;R50;
1;23k2 0.1%;R_0805_2012Metric;R55;
1;32k4 0.1%;R_0805_2012Metric;R56;
1;232k 0.1%;R_0805_2012Metric;R57;
1;48k7 0.1%;R_0805_2012Metric;R59;
1;1k;R_0805_2012Metric;R6;
1;10k7 0.1%;R_0805_2012Metric;R60;
1;16k9 0.1%;R_0805_2012Metric;R61;
5;40k2 0.1%;R_0805_2012Metric;R64 R86 R108 R130 R152;
5;30k1 0.1%;R_0805_2012Metric;R66 R88 R110 R132 R154;damping R0: Q = 0,3/alpha (§4.3)
10;100k 0.1%;R_0805_2012Metric;R68 R73 R90 R95 R112 R117 R134 R139 R156 R161;gate a (Vd + vc2)/2
30;100k 0.1%;R_0805_2012Metric;R69 R70 R71 R74 R75 R76 R91 R92 R93 R96 R97 R98 R113 R114 R115 R118 R119 R120 R135 R136 R137 R140 R141 R142 R157 R158 R159 R162 R163 R164;
2;150k 0.1%;R_0805_2012Metric;R7 R8;
2;117k 0.1%;R_0805_2012Metric;R72 R77;Ictl = |SH|/R: f0 proporzionale (replica-a.cir)
5;110 0.1%;R_0805_2012Metric;R78 R100 R122 R144 R166;alpha minima 0,099 (Q 3,0)
5;1k8 0.1%;R_0805_2012Metric;R79 R101 R123 R145 R167;
5;200 0.1%;R_0805_2012Metric;R80 R102 R124 R146 R168;x10
10;2k 0.1%;R_0805_2012Metric;R81 R82 R103 R104 R125 R126 R147 R148 R169 R170;
5;1k62 0.1%;R_0805_2012Metric;R83 R105 R127 R149 R171;
1;1k5;R_0805_2012Metric;R9;NOTA: ~6,7 mA nel riferimento (come il master)
4;110k 0.1%;R_0805_2012Metric;R94 R99 R138 R143;Ictl = |SH|/R: f0 proporzionale (replica-a.cir)
3;OPA1654AIDR;SOIC-14_3.9x8.7mm_P1.27mm;U1 U2 U3;buffer del pot POSITION, shaper, riferimento di drain
2;OPA1654AIDR;SOIC-14_3.9x8.7mm_P1.27mm;U11 U12;cella 3: summer, integratori, buffer, servo replica, uscita
2;OPA1654AIDR;SOIC-14_3.9x8.7mm_P1.27mm;U14 U15;cella 4: summer, integratori, buffer, servo replica, uscita
1;LM317;TO-220-3_Vertical;U140;
1;LM337;TO-220-3_Vertical;U141;
1;78L15;SOT-89-3;U142;
1;79L15;SOT-89-3;U143;
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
